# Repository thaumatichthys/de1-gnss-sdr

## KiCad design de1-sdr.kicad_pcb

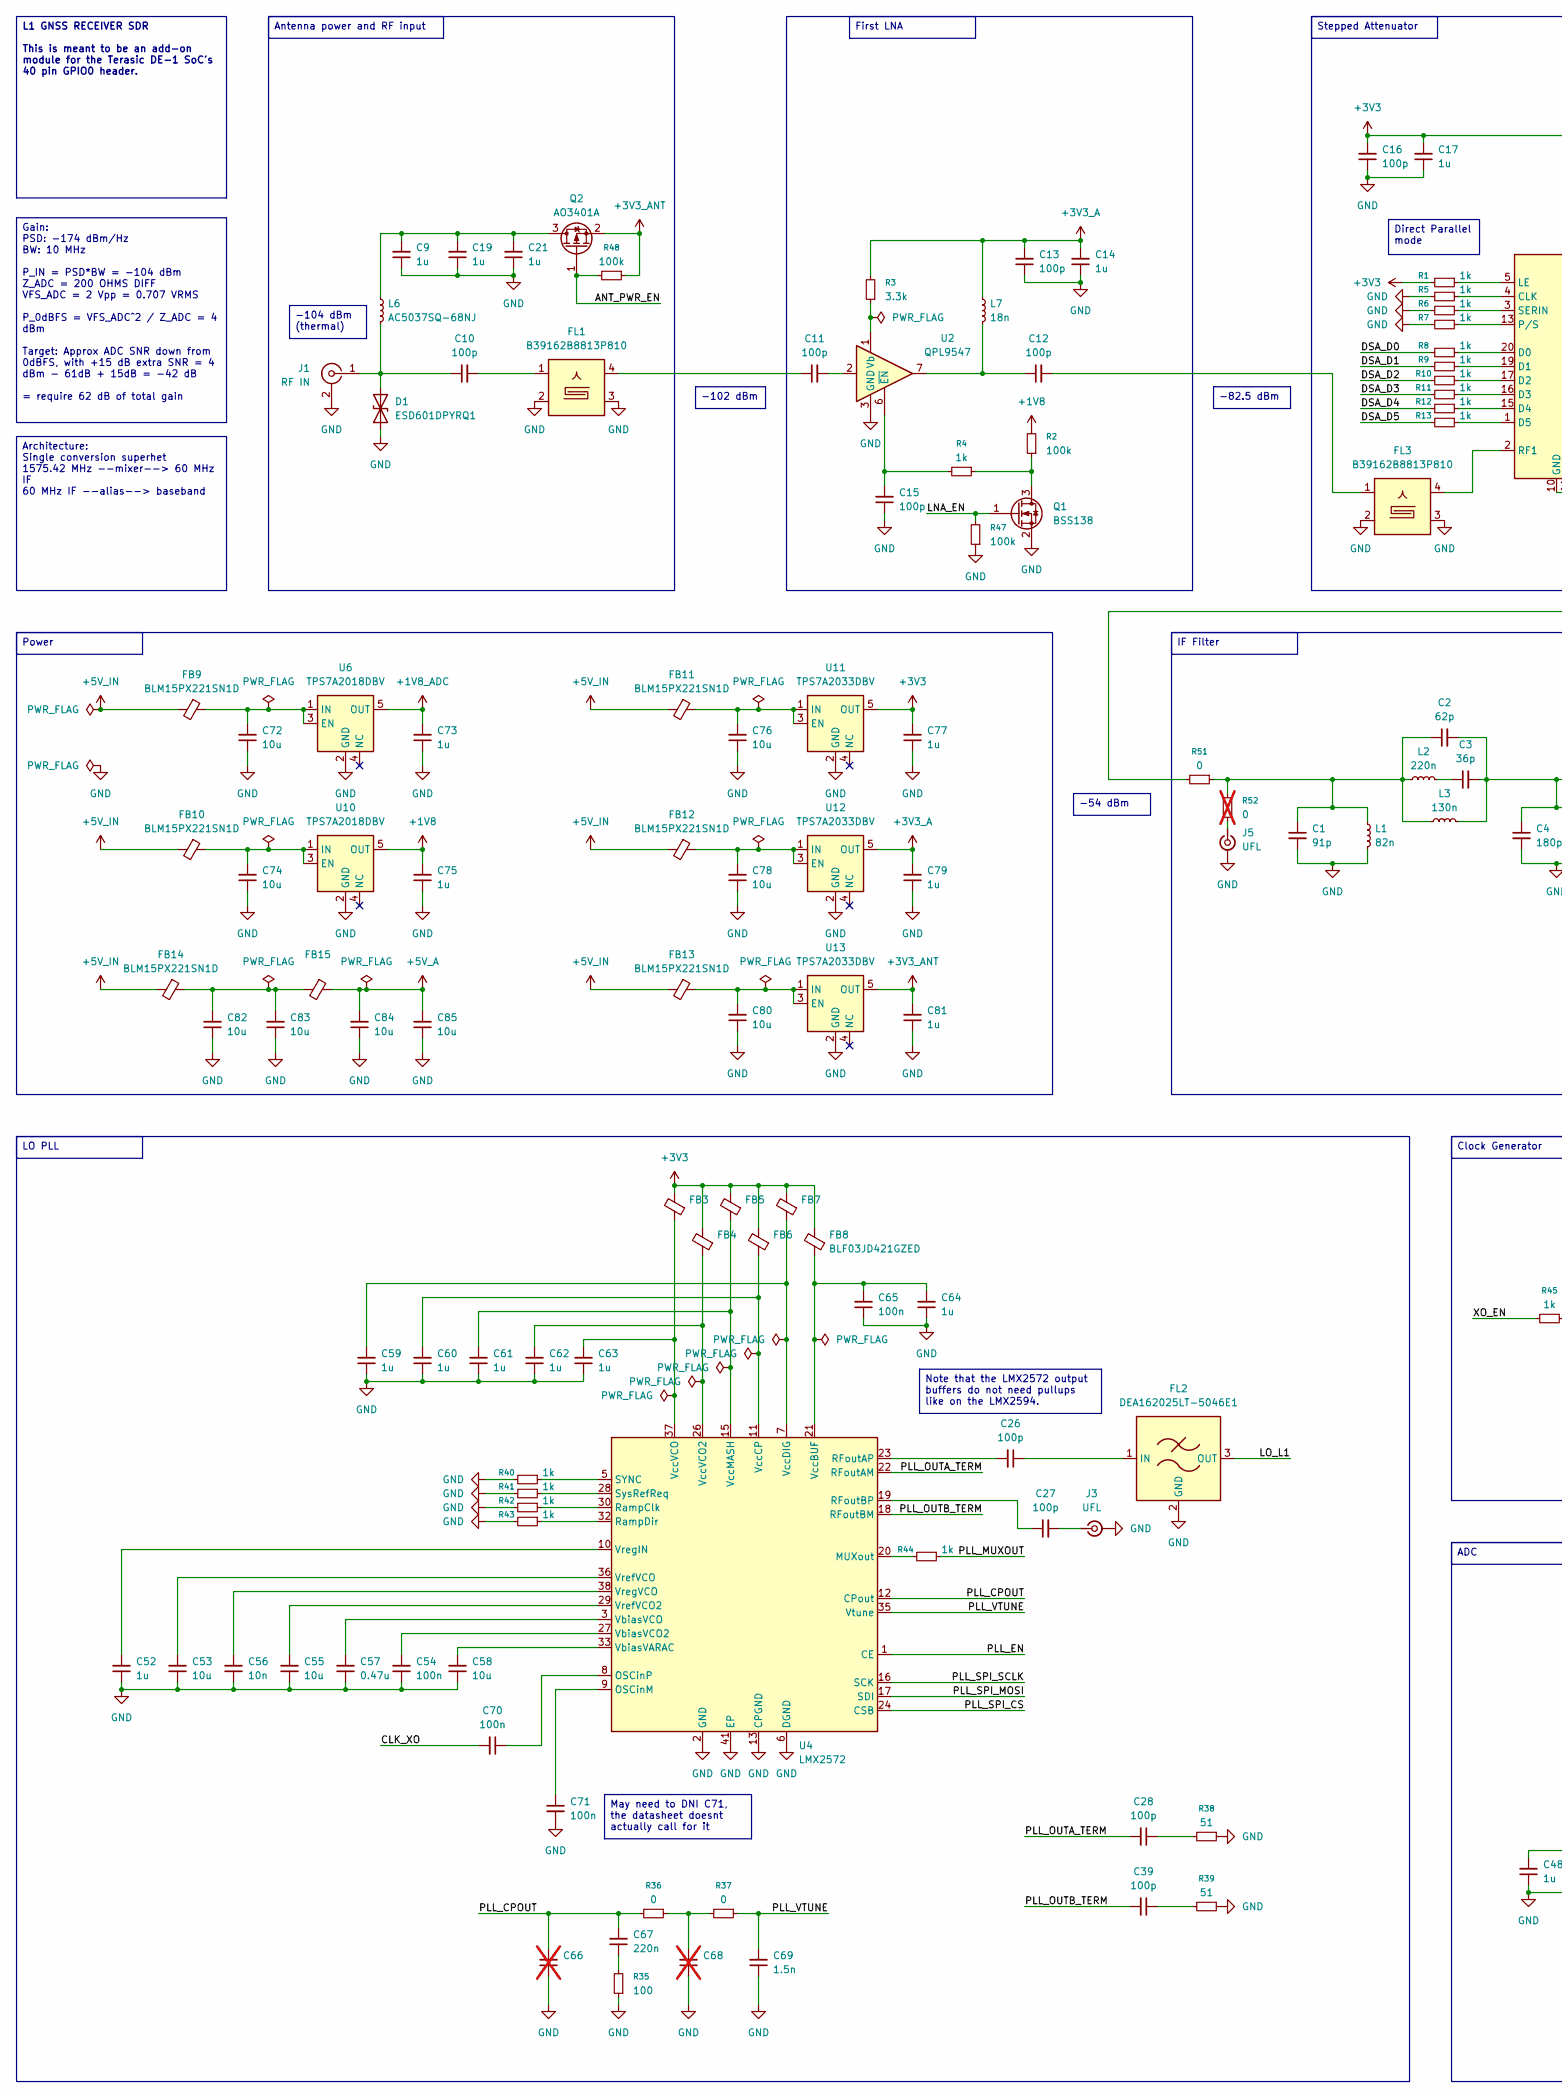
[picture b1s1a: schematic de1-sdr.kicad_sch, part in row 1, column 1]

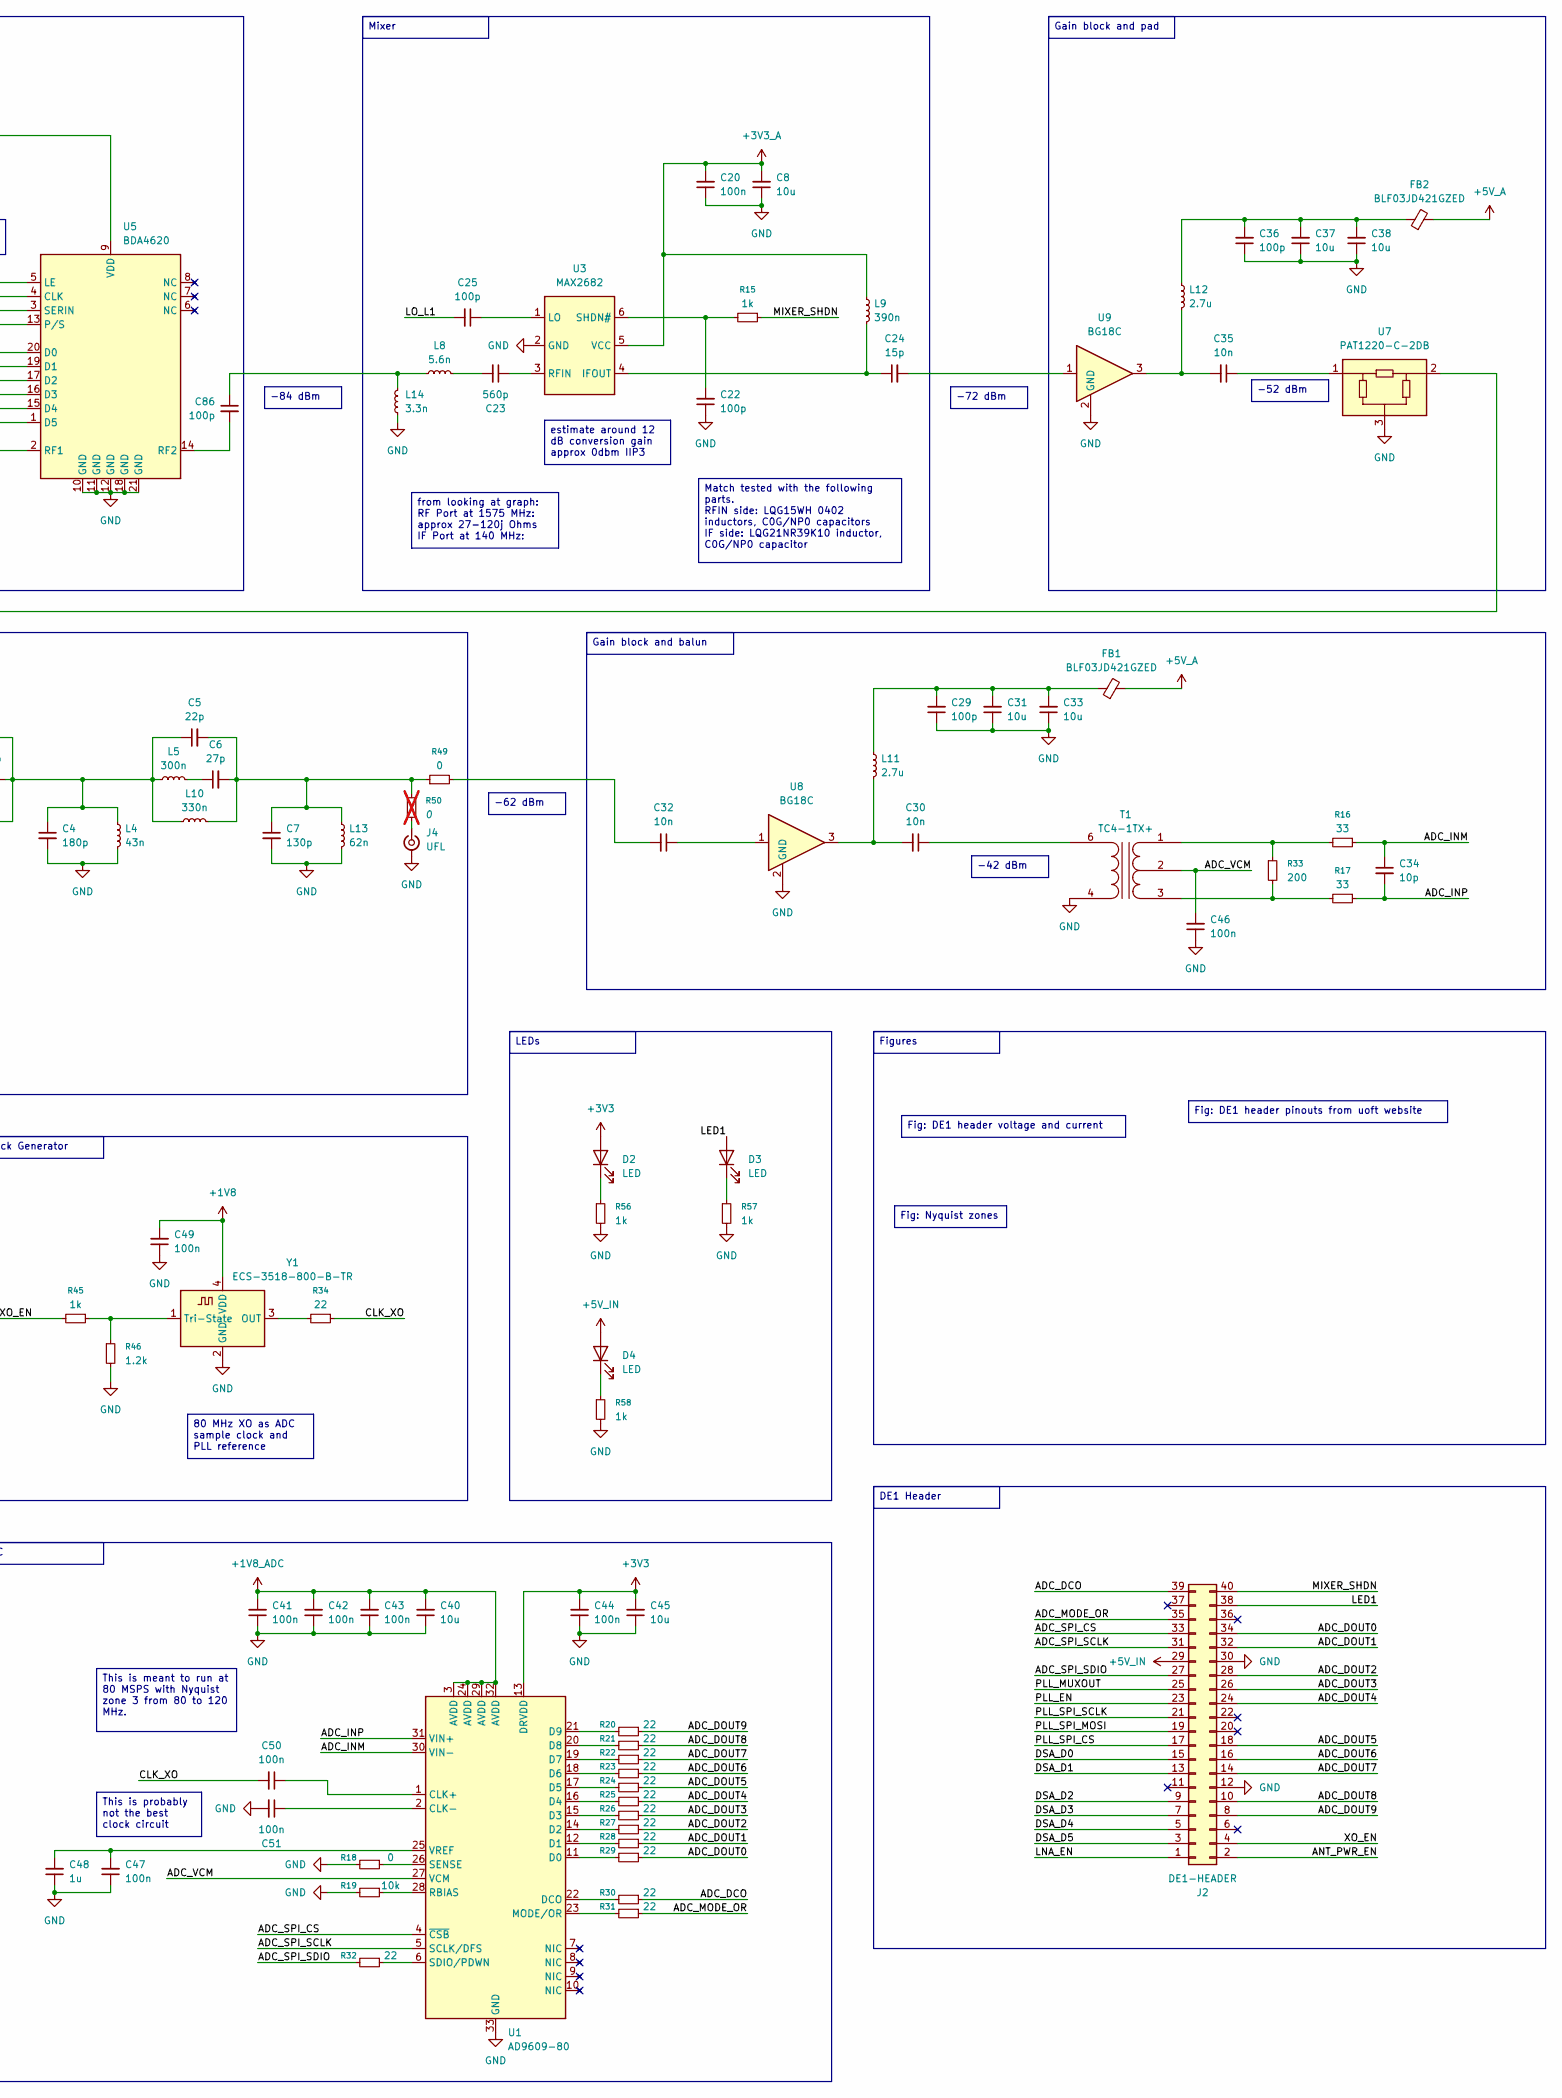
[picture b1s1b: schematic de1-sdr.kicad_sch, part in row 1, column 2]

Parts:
C1: 91p; C_0402_1005Metric
C2: 62p; C_0402_1005Metric
C3: 36p; C_0402_1005Metric
C4: 180p; C_0402_1005Metric
C5: 22p; C_0402_1005Metric
C6: 27p; C_0402_1005Metric
C7: 130p; C_0402_1005Metric
C8, C31, C33, C37, C38, C40, C45, C53, C55, C58, C72, C74, C76, C78, C80, C82, C83, C84, C85: 10u; C_0603_1608Metric
C9, C14, C17, C19, C21: 1u; C_0402_1005Metric
C10, C11, C12, C13, C15, C16, C22, C25, C26, C27, C28, C29, C36, C39, C86: 100p; C_0402_1005Metric
C20, C41, C42, C43, C44, C46, C47, C49, C50, C51, C54, C65, C70, C71: 100n; C_0402_1005Metric
C23: 560p; C_0402_1005Metric
C24: 15p; C_0402_1005Metric
C30, C32, C35, C56: 10n; C_0402_1005Metric
C34: 10p; C_0402_1005Metric
C48, C52, C59, C60, C61, C62, C63, C64, C73, C75, C77, C79, C81: 1u; C_0603_1608Metric
C57: 0.47u; C_0603_1608Metric
C66, C68: C_0402_1005Metric; not fitted
C67: 220n; C_0402_1005Metric
C69: 1.5n; C_0402_1005Metric
D1: ESD601DPYRQ1; D_0402_1005Metric
D2, D3, D4: LED; LED_0603_1608Metric
FB1, FB2, FB3, FB4, FB5, FB6, FB7, FB8: BLF03JD421GZED; L_0201_0603Metric
FB9, FB10, FB11, FB12, FB13, FB14, FB15: BLM15PX221SN1D; L_0402_1005Metric
FL1, FL3: B39162B8813P810; Filter_1109-5_1.1x0.9mm
FL2: DEA162025LT-5046E1; FILTER_TDK_0402
J1: RF IN; ADAMTECH_RF2-143-T-17-50-G_IMPROVED
J2: DE1-HEADER; IDC-Header_2x20_P2.54mm_Vertical
J3, J4, J5: UFL; U.FL_Molex_MCRF_73412-0110_Vertical
L1: 82n; L_0805_2012Metric
L2: 220n; L_0805_2012Metric
L3: 130n; L_0805_2012Metric
L4: 43n; L_0603_1608Metric
L5: 300n; L_0805_2012Metric
L6: AC5037SQ-68NJ
L7: 18n; L_0805_2012Metric
L8: 5.6n; L_0402_1005Metric
L9: 390n; L_0805_2012Metric
L10: 330n; L_1008_2520Metric
L11, L12: 2.7u; L_1210_3225Metric
L13: 62n; L_0603_1608Metric
L14: 3.3n; L_0402_1005Metric
Q1: BSS138; SOT-23
Q2: AO3401A; SOT-23
R1, R5, R6, R7, R8, R9, R10, R11, R12, R13: 1k; R_0201_0603Metric
R2, R47, R48: 100k; R_0402_1005Metric
R3: 3.3k; R_0402_1005Metric
R4, R15, R40, R41, R42, R43, R44, R45, R56, R57, R58: 1k; R_0402_1005Metric
R16, R17: 33; R_0402_1005Metric
R18, R36, R37, R49, R51: 0; R_0402_1005Metric
R19: 10k; R_0402_1005Metric
R20, R21, R22, R23, R24, R25, R26, R27, R28, R29, R30, R31, R32: 22; R_0201_0603Metric
R33: 200; R_0402_1005Metric
R34: 22; R_0402_1005Metric
R35: 100; R_0402_1005Metric
R38, R39: 51; R_0402_1005Metric
R46: 1.2k; R_0402_1005Metric
R50, R52: 0; R_0402_1005Metric; not fitted
T1: TC4-1TX+; Transformer_MiniCircuits_AT224-1A
U1: AD9609-80; QFN-32-1EP_5x5mm_P0.5mm_EP3.45x3.45mm
U2: QPL9547; DFN-8-1EP_2x2mm_P0.5mm_EP0.8x1.6mm
U3: MAX2682; SOT-23-6
U4: LMX2572; HVQFN-40-1EP_6x6mm_P0.5mm_EP4.1x4.1mm
U5: BDA4620; QFN-20-1EP_4x4mm_P0.5mm_EP2.5x2.5mm
U6, U10: TPS7A2018DBV; SOT-23-5
U7: PAT1220-C-2DB; RF_Attenuator_Susumu_PAT1220
U8, U9: BG18C; SOT-89-3
U11, U12, U13: TPS7A2033DBV; SOT-23-5
Y1: ECS-3518-800-B-TR; Oscillator_SMD_EuroQuartz_XO53-4Pin_5.0x3.2mm

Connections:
+1V8: C49.2, C75.2, R2.2, U10.5 (OUT), Y1.4 (VDD)
+1V8_ADC: C40.2, C41.2, C42.2, C43.2, C73.2, U1.3 (AVDD), U1.24 (AVDD), U1.29 (AVDD), U1.32 (AVDD), U6.5 (OUT)
+3V3: C16.2, C17.2, C44.2, C45.2, C77.2, D2.2 (A), FB3.2, FB4.2, FB5.2, FB6.2, FB7.2, FB8.2, R1.2, U1.13 (DRVDD), U5.9 (VDD), U11.5 (OUT)
+3V3_A: C8.2, C13.2, C14.2, C20.2, C79.2, L7.1, L9.1, R3.2, U3.5 (VCC), U12.5 (OUT)
+3V3_ANT: C81.2, Q2.2 (S), R48.1, U13.5 (OUT)
+5V_A: C84.2, C85.2, FB1.2, FB2.2, FB15.1
+5V_IN: D4.2 (A), FB9.2, FB10.2, FB11.2, FB12.2, FB13.2, FB14.2, J2.29
/ADC_DCO: J2.39, R30.1
/ADC_DOUT0: J2.34, R29.1
/ADC_DOUT1: J2.32, R28.1
/ADC_DOUT2: J2.28, R27.1
/ADC_DOUT3: J2.26, R26.1
/ADC_DOUT4: J2.24, R25.1
/ADC_DOUT5: J2.18, R24.1
/ADC_DOUT6: J2.16, R23.1
/ADC_DOUT7: J2.14, R22.1
/ADC_DOUT8: J2.10, R21.1
/ADC_DOUT9: J2.8, R20.1
/ADC_INM: C34.1, R16.1, U1.30 (VIN-)
/ADC_INP: C34.2, R17.1, U1.31 (VIN+)
/ADC_MODE_OR: J2.35, R31.1
/ADC_SPI_CS: J2.33, U1.4 (~CSB)
/ADC_SPI_SCLK: J2.31, U1.5 (SCLK/DFS)
/ADC_SPI_SDIO: J2.27, R32.2
/ADC_VCM: C46.2, T1.2 (CT), U1.27 (VCM)
/ANT_PWR_EN: J2.2, Q2.1 (G), R48.2
/CLK_XO: C50.2, C70.2, R34.1
/DSA_D0: J2.15, R8.2
/DSA_D1: J2.13, R9.2
/DSA_D2: J2.9, R10.2
/DSA_D3: J2.7, R11.2
/DSA_D4: J2.5, R12.2
/DSA_D5: J2.3, R13.2
/LED1: D3.2 (A), J2.38
/LNA_EN: J2.1, Q1.1 (G), R47.2
/LO_L1: C25.2, FL2.3 (OUT)
/MIXER_SHDN: J2.40, R15.1
/PLL_CPOUT: C66.2, C67.2, R36.2, U4.12 (CPout)
/PLL_EN: J2.23, U4.1 (CE)
/PLL_MUXOUT: J2.25, R44.1
/PLL_OUTA_TERM: C28.2, U4.22 (RFoutAM)
/PLL_OUTB_TERM: C39.2, U4.18 (RFoutBM)
/PLL_SPI_CS: J2.17, U4.24 (CSB)
/PLL_SPI_MOSI: J2.19, U4.17 (SDI)
/PLL_SPI_SCLK: J2.21, U4.16 (SCK)
/PLL_VTUNE: C69.2, R37.1, U4.35 (Vtune)
/XO_EN: J2.4, R45.2
GND: C1.2, C4.2, C7.2, C8.1, C9.1, C13.1, C14.1, C15.1, C16.1, C17.1, C19.1, C20.1, C21.1, C22.1, C29.1, C31.1, C33.1, C36.1, C37.1, C38.1, C40.1, C41.1, C42.1, C43.1, C44.1, C45.1, C46.1, C47.1, C48.1, C49.1, C51.2, C52.1, C53.1, C54.1, C55.1, C56.1, C57.1, C58.1, C59.1, C60.1, C61.1, C62.1, C63.1, C64.1, C65.1, C66.1, C68.1, C69.1, C71.2, C72.1, C73.1, C74.1, C75.1, C76.1, C77.1, C78.1, C79.1, C80.1, C81.1, C82.1, C83.1, C84.1, C85.1, D1.1 (A1), FL1.2, FL1.3, FL1.5, FL2.2 (GND), FL2.4 (GND), FL3.2, FL3.3, FL3.5, J1.2 (Ext), J2.12, J2.30, J3.2 (Ext), J4.2 (Ext), J5.2 (Ext), L1.2, L4.2, L13.2, L14.1, Q1.2 (S), R5.2, R6.2, R7.2, R18.2, R19.2, R35.1, R38.1, R39.1, R40.2, R41.2, R42.2, R43.2, R46.2, R47.1, R56.2, R57.2, R58.2, T1.4, U1.33 (GND), U2.3 (GND), U2.4 (GND), U2.5 (GND), U2.8 (GND), U2.9 (GND), U3.2 (GND), U4.2 (GND), U4.4 (GND), U4.6 (DGND), U4.13 (CPGND), U4.14 (DGND), U4.25 (GND), U4.31 (GND), U4.34 (GND), U4.39 (GND), U4.40 (GND), U4.41 (EP), U5.10 (GND), U5.11 (GND), U5.12 (GND), U5.18 (GND), U5.21 (GND), U6.2 (GND), U7.3, U8.2 (GND_2), U9.2 (GND_2), U10.2 (GND), U11.2 (GND), U12.2 (GND), U13.2 (GND), Y1.2 (GND)
unnamed: C1.1, C2.1, L1.1, L2.1, L3.1, R51.1, R52.1
unnamed: C2.2, C3.2, C4.1, C5.1, L3.2, L4.1, L5.1, L10.1
unnamed: C3.1, L2.2
unnamed: C5.2, C6.2, C7.1, L10.2, L13.1, R49.1, R50.1
unnamed: C6.1, L5.2
unnamed: C10.2, FL1.1
unnamed: C11.1, FL1.4
unnamed: C11.2, U2.2
unnamed: C12.1, L7.2, U2.7
unnamed: C12.2, FL3.1
unnamed: C23.2, L8.2
unnamed: C24.2, U9.1
unnamed: C28.1, R38.2
unnamed: C29.2, C31.2, C33.2, FB1.1, L11.1
unnamed: C30.1, T1.6
unnamed: C30.2, L11.2, U8.3
unnamed: C32.1, U8.1
unnamed: C32.2, R49.2
unnamed: C35.1, U7.1
unnamed: C35.2, L12.2, U9.3
unnamed: C36.2, C37.2, C38.2, FB2.1, L12.1
unnamed: C39.1, R39.2
unnamed: C67.1, R35.2
unnamed: C68.2, R36.1, R37.2
unnamed: C82.2, C83.2, FB14.1, FB15.2
unnamed: C86.1, L8.1, L14.2
unnamed: C10.1, D1.2 (A2), J1.1 (In), L6.2
unnamed: D2.1 (K), R56.1
unnamed: D3.1 (K), R57.1
unnamed: D4.1 (K), R58.1
unnamed: C26.1, FL2.1 (IN)
unnamed: C27.2, J3.1 (In)
unnamed: J4.1 (In), R50.2
unnamed: J5.1 (In), R52.2
unnamed: Q1.3 (D), R2.1, R4.1
unnamed: C9.2, C19.2, C21.2, L6.1, Q2.3 (D)
unnamed: R16.2, R33.1, T1.1 (S)
unnamed: R17.2, R33.2, T1.3 (S)
unnamed: R51.2, U7.2
unnamed: C50.1, U1.1 (CLK+)
unnamed: C51.1, U1.2 (CLK-)
unnamed: R29.2, U1.11 (D0)
unnamed: R28.2, U1.12 (D1)
unnamed: R27.2, U1.14 (D2)
unnamed: R26.2, U1.15 (D3)
unnamed: R25.2, U1.16 (D4)
unnamed: R24.2, U1.17 (D5)
unnamed: R23.2, U1.18 (D6)
unnamed: R22.2, U1.19 (D7)
unnamed: R21.2, U1.20 (D8)
unnamed: R20.2, U1.21 (D9)
unnamed: R30.2, U1.22 (DCO)
unnamed: R31.2, U1.23 (MODE/OR)
unnamed: R19.1, U1.28 (RBIAS)
unnamed: R32.1, U1.6 (SDIO/PDWN)
unnamed: R18.1, U1.26 (SENSE)
unnamed: C47.2, C48.2, U1.25 (VREF)
unnamed: R3.1, U2.1 (Vb)
unnamed: C15.2, R4.2, U2.6 (~EN)
unnamed: C24.1, L9.2, U3.4 (IFOUT)
unnamed: C25.1, U3.1 (LO)
unnamed: C23.1, U3.3 (RFIN)
unnamed: C22.2, R15.2, U3.6 (SHDN#)
unnamed: R44.2, U4.20 (MUXout)
unnamed: C71.1, U4.9 (OSCinM)
unnamed: C70.1, U4.8 (OSCinP)
unnamed: C26.2, U4.23 (RFoutAP)
unnamed: C27.1, U4.19 (RFoutBP)
unnamed: R42.1, U4.30 (RampClk)
unnamed: R43.1, U4.32 (RampDir)
unnamed: R40.1, U4.5 (SYNC)
unnamed: R41.1, U4.28 (SysRefReq)
unnamed: C58.2, U4.33 (VbiasVARAC)
unnamed: C54.2, U4.27 (VbiasVCO2)
unnamed: C57.2, U4.3 (VbiasVCO)
unnamed: C64.2, C65.2, FB8.1, U4.21 (VccBUF)
unnamed: C60.2, FB6.1, U4.11 (VccCP)
unnamed: C59.2, FB7.1, U4.7 (VccDIG)
unnamed: C61.2, FB5.1, U4.15 (VccMASH)
unnamed: C62.2, FB4.1, U4.26 (VccVCO2)
unnamed: C63.2, FB3.1, U4.37 (VccVCO)
unnamed: C55.2, U4.29 (VrefVCO2)
unnamed: C53.2, U4.36 (VrefVCO)
unnamed: C52.2, U4.10 (VregIN)
unnamed: C56.2, U4.38 (VregVCO)
unnamed: R5.1, U5.4 (CLK)
unnamed: R8.1, U5.20 (D0)
unnamed: R9.1, U5.19 (D1)
unnamed: R10.1, U5.17 (D2)
unnamed: R11.1, U5.16 (D3)
unnamed: R12.1, U5.15 (D4)
unnamed: R13.1, U5.1 (D5)
unnamed: R1.1, U5.5 (LE)
unnamed: R7.1, U5.13 (P/S)
unnamed: FL3.4, U5.2 (RF1)
unnamed: C86.2, U5.14 (RF2)
unnamed: R6.1, U5.3 (SERIN)
unnamed: C72.2, FB9.1, U6.1 (IN), U6.3 (EN)
unnamed: C74.2, FB10.1, U10.1 (IN), U10.3 (EN)
unnamed: C76.2, FB11.1, U11.1 (IN), U11.3 (EN)
unnamed: C78.2, FB12.1, U12.1 (IN), U12.3 (EN)
unnamed: C80.2, FB13.1, U13.1 (IN), U13.3 (EN)
unnamed: R34.2, Y1.3 (OUT)
unnamed: R45.1, R46.1, Y1.1 (Tri-State)

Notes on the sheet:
Clock Generator
Mixer
Gain: PSD: -174 dBm/Hz BW: 10 MHz P_IN = PSD*BW = -104 dBm Z_ADC = 200 OHMS DIFF VFS_ADC = 2 Vpp = 0.707 VRMS P_0dBFS = VFS_ADC^2 / Z_ADC = 4 dBm Target: Approx ADC SNR down from 0dBFS, with +15 dB extra SNR = 4 dBm - 61dB + 15dB = -42 dB = require 62 dB of total gain
-42 dBm
LO PLL
Direct Parallel mode
IF Filter
Fig: Nyquist zones
May need to DNI C71, the datasheet doesnt actually call for it
from looking at graph: RF Port at 1575 MHz: approx 27-120j Ohms IF Port at 140 MHz:
estimate around 12 dB conversion gain approx 0dbm IIP3
DE1 Header
-102 dBm
Gain block and balun
Power
First LNA
Stepped Attenuator
80 MHz XO as ADC sample clock and PLL reference
This is meant to run at 80 MSPS with Nyquist zone 3 from 80 to 120 MHz.
Fig: DE1 header pinouts from uoft website
-54 dBm
-52 dBm
-84 dBm
-72 dBm
Match tested with the following parts. RFIN side: LQG15WH 0402 inductors, C0G/NP0 capacitors IF side: LQG21NR39K10 inductor, C0G/NP0 capacitor
LEDs
L1 GNSS RECEIVER SDR This is meant to be an add-on module for the Terasic DE-1 SoC's 40 pin GPIO0 header.
Figures
Antenna power and RF input
-62 dBm
This is probably not the best clock circuit
ADC
-104 dBm (thermal)
-82.5 dBm
Note that the LMX2572 output buffers do not need pullups like on the LMX2594.
Fig: DE1 header voltage and current
Gain block and pad
Architecture: Single conversion superhet 1575.42 MHz --mixer--> 60 MHz IF 60 MHz IF --alias--> baseband

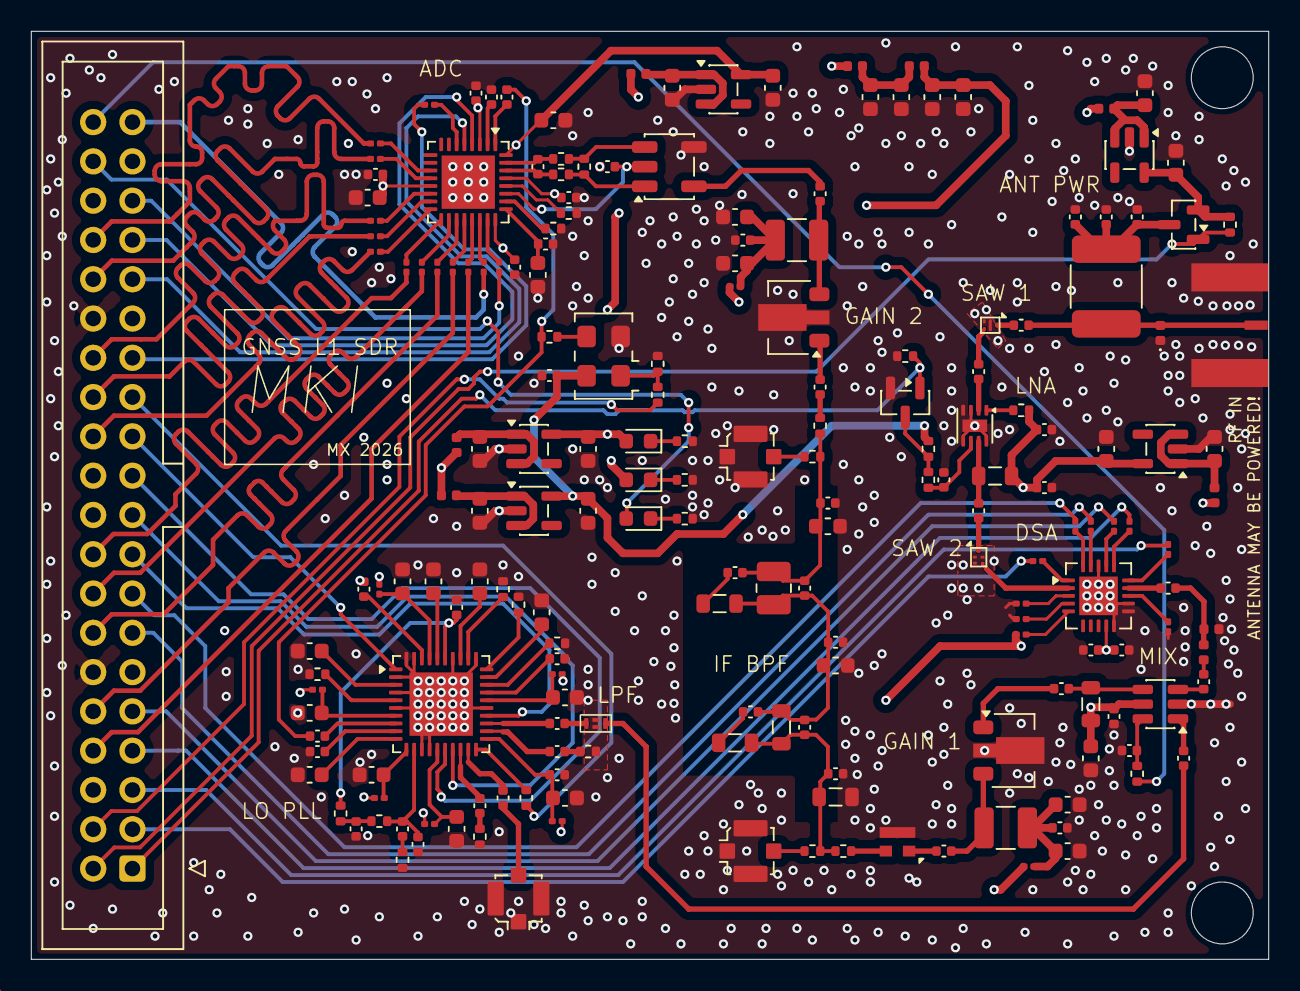
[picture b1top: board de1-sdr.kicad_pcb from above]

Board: 4 copper layers, 80.0 x 60.0 mm, 197 parts (0 on the bottom side), 152 nets.
